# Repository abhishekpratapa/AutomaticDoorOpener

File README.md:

# AutomaticDoorOpener
A hardware device to open a door automatically through Bluetooth and the Internet

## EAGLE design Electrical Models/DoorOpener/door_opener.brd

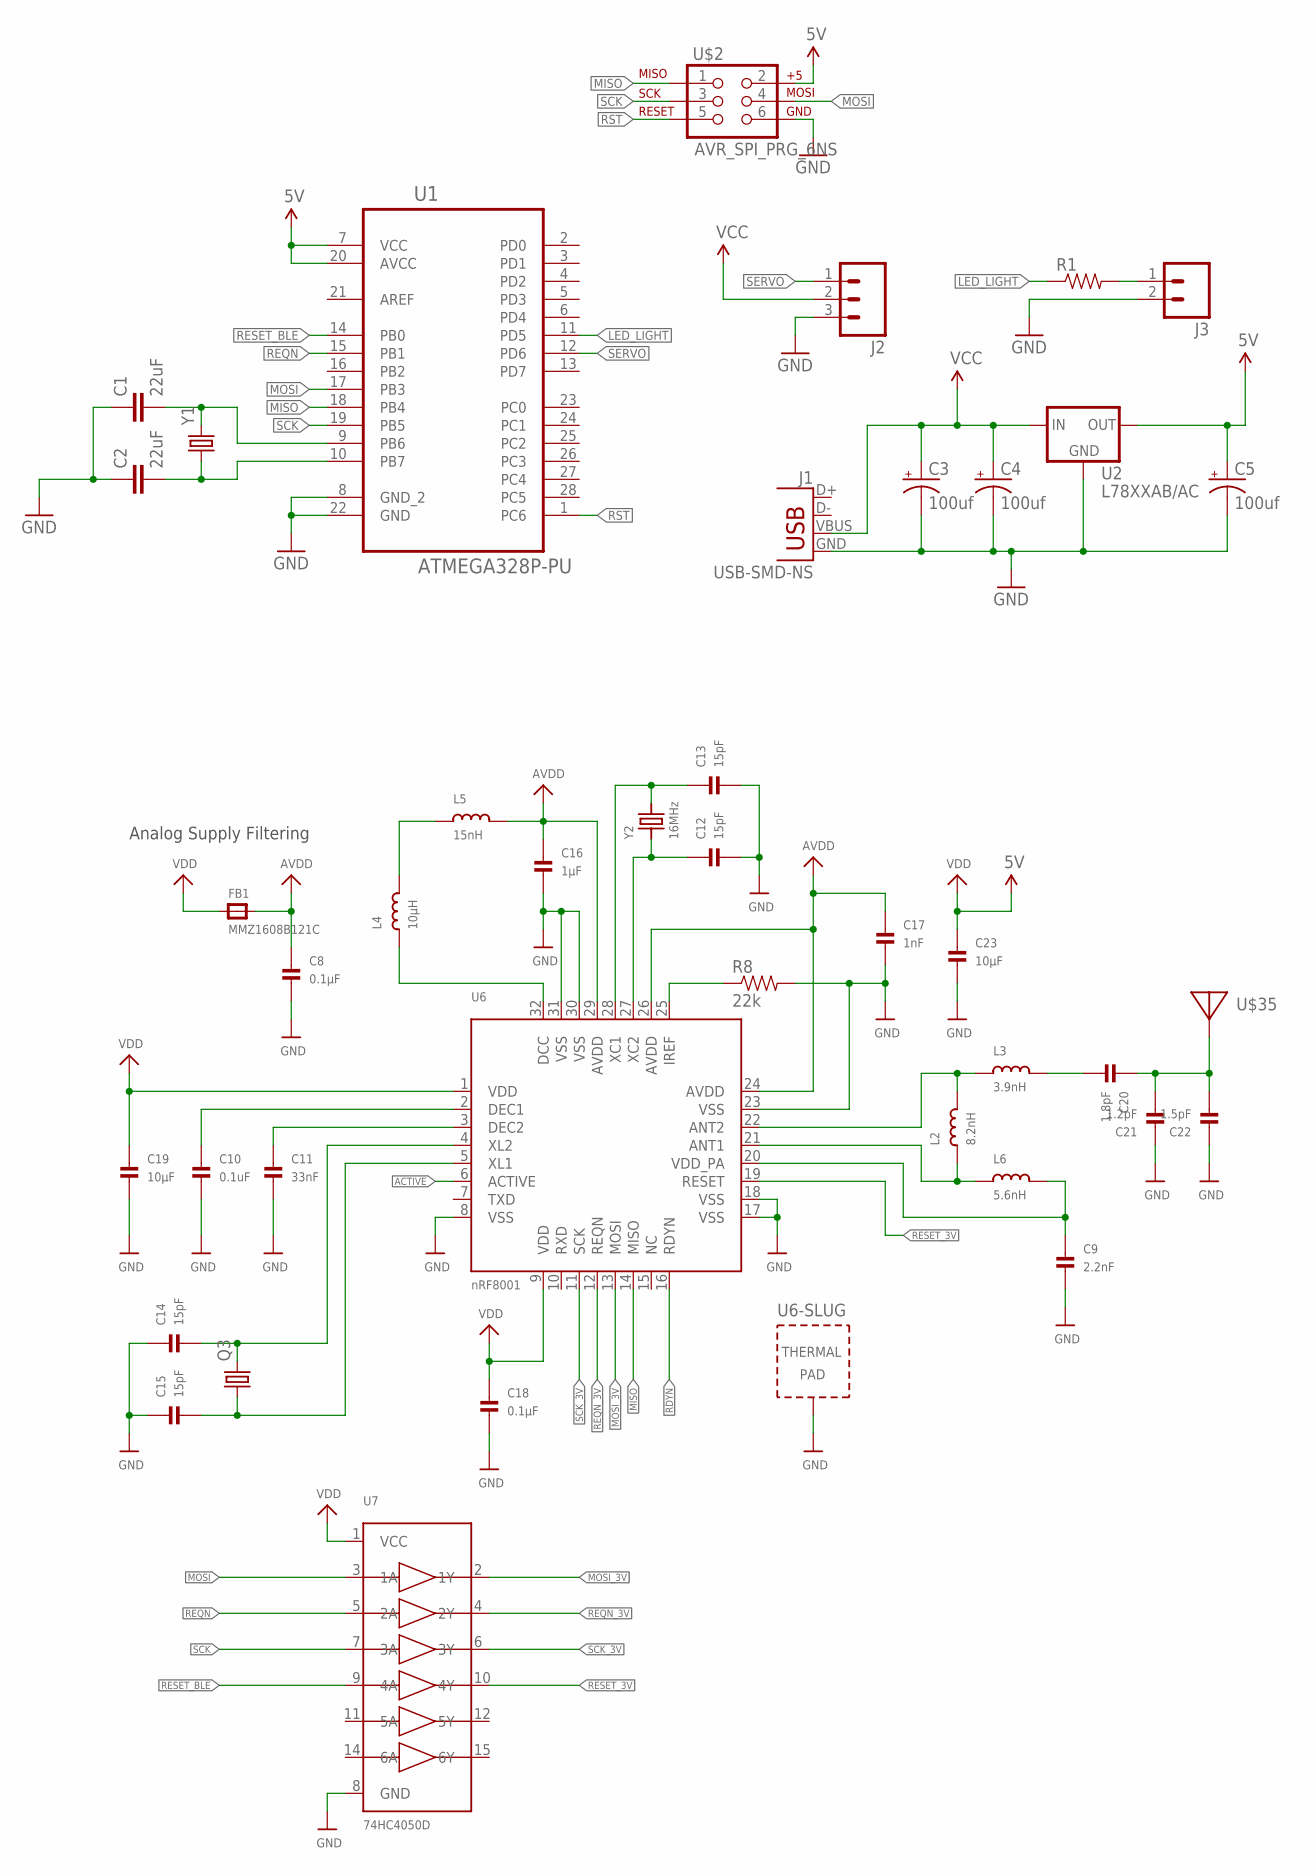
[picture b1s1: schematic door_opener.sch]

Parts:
C1, C2: 22uF; 1210
C3, C4, C5: 100uf; NIPPON_F80
C8, C18: 0.1µF; 0402
C9: 2.2nF; _0402
C10: 0.1uF; 0402
C11: 33nF; 0402
C12, C13, C14, C15: 15pF; 0402
C16: 1µF; 0402
C17: 1nF; _0603
C19, C23: 10µF; 0402
C20: 1.8pF; _0402MP
C21: 1.2pF; _0402MP
C22: 1.5pF; _0402MP
FB1: MMZ1608B121C; 0805
J1: USB-SMD-NS; USB-MINIB-NOSTOP
J2: M031X03_NO_SILK; 1X03_NO_SILK
J3: M021X02_NO_SILK; 1X02_NO_SILK
L2: 8.2nH; _0402
L3: 3.9nH; _0402
L4: 10µH; _0603
L5: 15nH; _0603
L6: 5.6nH; _0402
Q3: CRYSTAL5X3; CRYSTAL-SMD-5X3
R1: RESISTOR1206; 1206
R8: 22k; 0805
U1: ATMEGA328P-PU; DIP254P762X457-28
U2: L78XXAB/AC; 78XXL
U6: nRF8001; QFN32_5MM
U7: 74HC4050D; TSSOP16
U$2: AVR_SPI_PRG_6NS; 2X3-NS
U$35: ANTENNA_PCBNRF8001_1.6MM; ANT_PCB_2.4GHZ_NRF8001_1.6MM_1OZ
Y1: CRYSTALHC49US; HC49US
Y2: 16MHz; CRYSTAL_3.2X2.5

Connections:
5V: C5.+, C23.1, U1.7 (VCC), U1.20 (AVCC), U2.OUT, U$2.2
+3.3V: C18.1, C19.1, FB1.1, U6.1 (VDD), U6.9 (VDD), U7.1 (VCC)
ACTIVE: U6.6 (ACTIVE)
AVDD: C8.1, C16.1, C17.1, FB1.2, L5.2, U6.24 (AVDD), U6.26 (AVDD), U6.29 (AVDD)
GND: C1.1, C2.1, C3.-, C4.-, C5.-, C8.2, C9.2, C10.2, C11.2, C12.2, C13.2, C14.1, C15.1, C16.2, C17.2, C18.2, C19.2, C21.1, C22.1, C23.2, J1.GND, J2.3, J3.2, R8.2, U1.8 (GND_2), U1.22 (GND), U2.GND, U6.8 (VSS), U6.17 (VSS), U6.18 (VSS), U6.23 (VSS), U6.30 (VSS), U6.31 (VSS), U6.33 (TP), U7.8 (GND), U$2.6
LED_LIGHT: R1.1, U1.11 (PD5)
MISO: U1.18 (PB4), U6.14 (MISO), U$2.1
MOSI: U1.17 (PB3), U7.3 (1A), U$2.4
MOSI_3V: U6.13 (MOSI), U7.2 (1Y)
unnamed: C1.2, U1.9 (PB6), Y1.2
unnamed: C2.2, U1.10 (PB7), Y1.1
unnamed: J3.1, R1.2
unnamed: C9.1, L6.2, U6.20 (VDD_PA)
unnamed: C11.1, U6.3 (DEC2)
unnamed: C10.1, U6.2 (DEC1)
unnamed: C13.1, U6.28 (XC1), Y2.2
unnamed: C12.1, U6.27 (XC2), Y2.1
unnamed: L4.1, U6.32 (DCC)
unnamed: R8.1, U6.25 (IREF)
unnamed: L4.2, L5.1
unnamed: L2.2, L3.1, U6.22 (ANT2)
unnamed: L2.1, L6.1, U6.21 (ANT1)
unnamed: C14.2, Q3.3 (2), U6.4 (XL2)
unnamed: C15.2, Q3.1, U6.5 (XL1)
unnamed: C20.2, L3.2
unnamed: C20.1, C21.2, C22.2, U$35.FEED
RDYN: U6.16 (RDYN)
REQN: U1.15 (PB1), U7.5 (2A)
REQN_3V: U6.12 (REQN), U7.4 (2Y)
RESET_3V: U6.19 (RESET), U7.10 (4Y)
RESET_BLE: U1.14 (PB0), U7.9 (4A)
RST: U1.1 (PC6), U$2.5
SCK: U1.19 (PB5), U7.7 (3A), U$2.3
SCK_3V: U6.11 (SCK), U7.6 (3Y)
SERVO: J2.1, U1.12 (PD6)
VCC: C3.+, C4.+, J1.VBUS, J2.2, U2.IN

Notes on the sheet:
Analog Supply Filtering

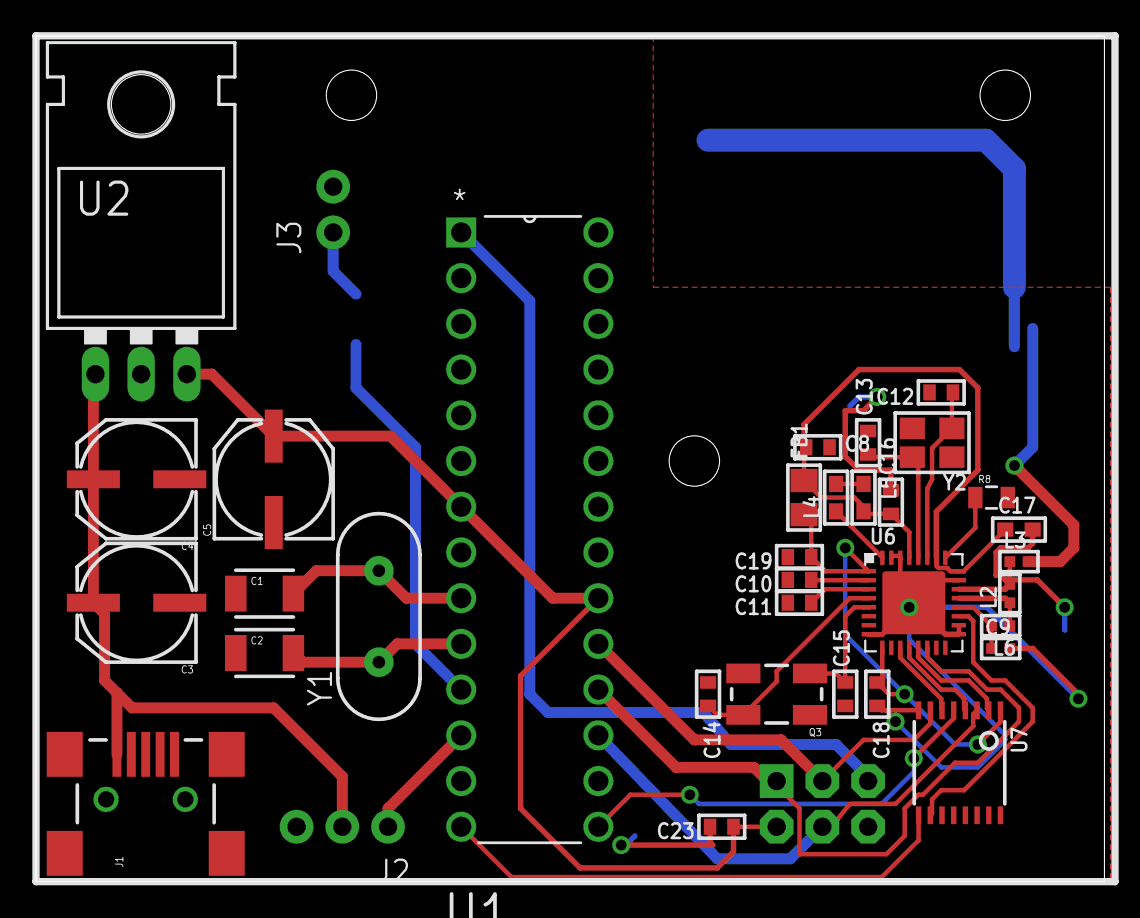
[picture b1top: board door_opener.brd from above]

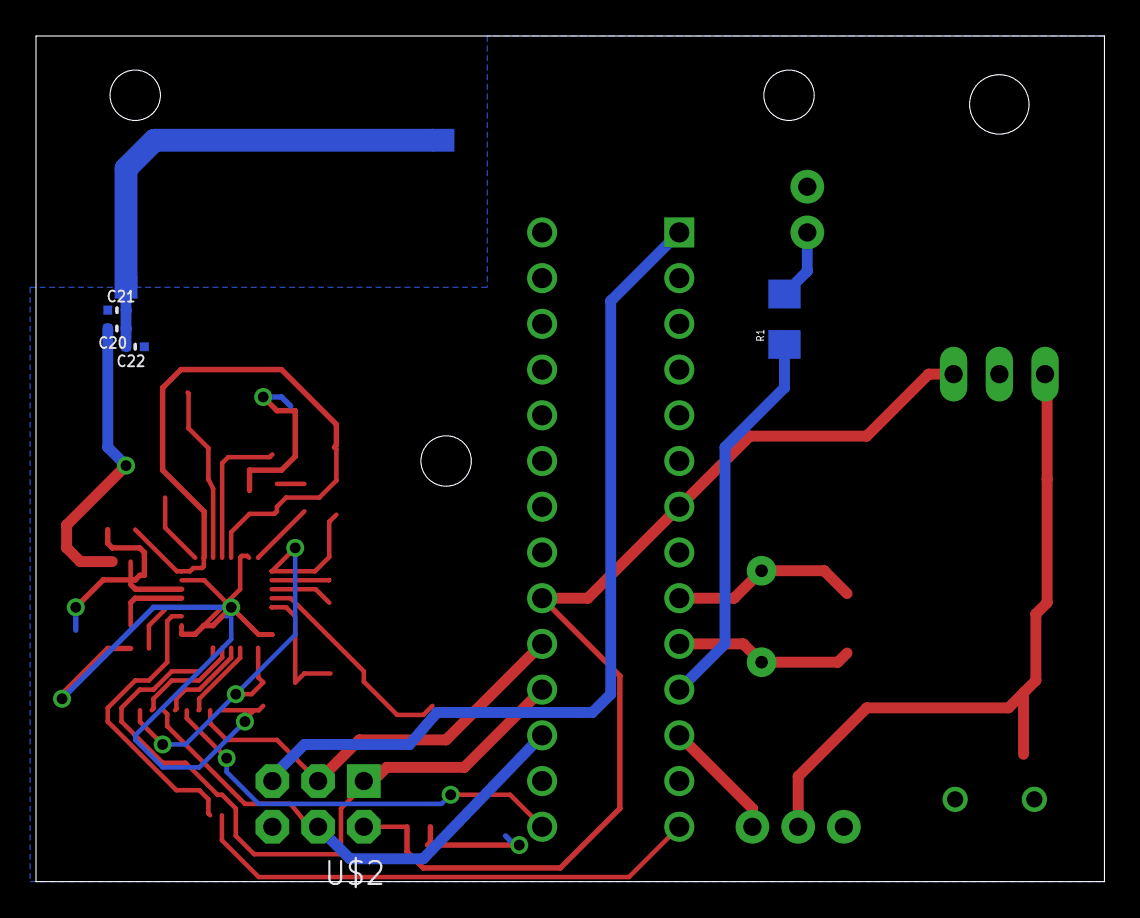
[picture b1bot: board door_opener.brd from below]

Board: 2 copper layers, 59.4 x 47.0 mm, 41 parts (6 on the bottom side), 34 nets.

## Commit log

2016-06-19 Added Name
2016-12-17 added electrical models
2016-12-17 added images
2016-12-20 Added images for the door opener

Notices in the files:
parts and their libraries:
SparkFun-Capacitors: Licensing: Creative Commons ShareAlike 4.0 International - https://creativecommons.org/licenses/by-sa/4.0
